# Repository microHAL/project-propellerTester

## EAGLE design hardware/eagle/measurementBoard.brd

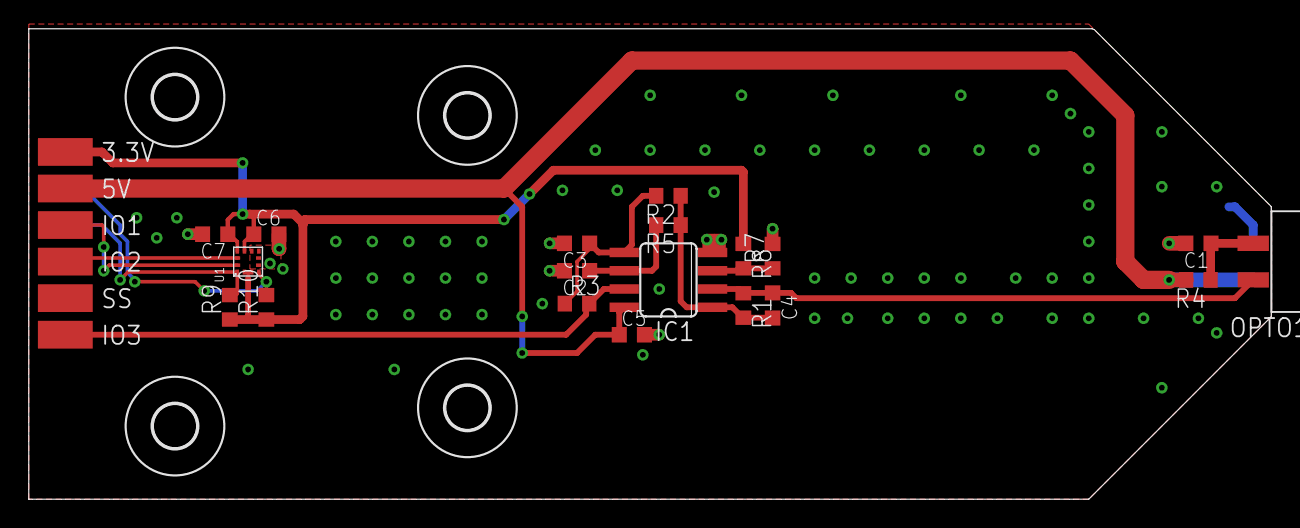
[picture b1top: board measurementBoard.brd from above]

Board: 2 copper layers, 86.3 x 32.7 mm, 25 parts (1 on the bottom side), 15 nets.

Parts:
C1: 2.2u; C0603K
C2: 10n; C0603K
C3, C4: 1n; C0603K
C5, C6, C7: 100n; C0603K
CON1: MICROHAL_CONNECTOR_M_1_REDUCED; MICROHAL_CONNECTOR_M_1_REDUCED_EDGE
H1, H2, H3, H4: MOUNT-HOLE3.0; 3,0
IC1: MAX989ESA; SO08
OPTO1: CNY70EDGE; CNY70_EDGE
R1, R6, R8: 3k; R0603
R2, R5: 100k; R0603
R3: 1M; R0603
R4: 100R; R0603
R7: DNF; R0603
R9, R10: 4.7k; R0603
U1: LGA-12

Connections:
+3V3: C6.1, C7.1, CON1.2, R8.1, R9.1, R10.1, U1.2, U1.3, U1.9, U1.10
+5V: C5.1, CON1.4, IC1.8, OPTO1.A, R4.2
GND: C1.2, C2.2, C3.2, C5.2, C6.2, C7.2, CON1.1, IC1.4, R6.2, R7.2, U1.5, U1.6, U1.7, U1.8
INT1: CON1.6, U1.12
INT2: CON1.8, U1.11
unnamed: C4.2, IC1.1, R1.2, R2.1, R5.1
unnamed: C4.1, IC1.2, OPTO1.E, R1.1
unnamed: C3.1, IC1.5, R2.2, R3.1
unnamed: C1.1, OPTO1.C, R4.1
unnamed: C2.1, IC1.6, R5.2
unnamed: OPTO1.K, R6.1
unnamed: IC1.3, R7.1, R8.2
OUT: CON1.12, IC1.7, R3.2
SCL: CON1.5, R9.2, U1.1
SDA: CON1.3, R10.2, U1.4

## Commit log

2016-01-26 Add initial directories
2016-01-26 added folders for propellerTester project
2016-01-30 Share project "Propeller tester firmware" into "https://svn.code.sf.net/p/microhal/drivers/Projects"
2016-01-30 added project template
2016-02-01 added measuring board
2016-02-06 added model of mechanical conception
2016-02-07 Added lis2dh12 and hx711 drivers to project.
2016-02-07 updated BSP configuration, enabled SPI and I2C device
2016-02-11 3D model updated
2016-02-13 added second version of hardware solution
2016-02-13 updated second version of mechanical montage
2016-02-15 added sk8 model
2016-03-18 added files to propellerTester PC application project
2016-03-22 Project creation.
2016-03-22 First sample program.
2016-03-22 Added linked resource - microHAL.
2016-03-27 added about dialog, changed main window gui
2016-03-27 Added class prototypes
2016-04-01 Added PCB project files, unfinished.
2016-04-01 Started implementing Timer interrupt in stepperMotor driver.
2016-04-01 Wired last connections.
2016-04-03 Probably ready for production.
2016-04-03 Rename.
2016-04-03 Rename, old files deletion.
2016-04-06 Modified connections between base SMT32F4-discovery and stepper motor driver.
2016-04-06 Instantiated a class for DRV8825.
2016-04-10 Added positionController class (draft).
2016-04-10 Added BT SPP source and header files (empty).
2016-04-10 Added diagnostic, configured and tested usart port.
2016-04-10 Added mutex, cosmetics.
2016-04-10 Added configuration for serial ports.
2016-04-10 Changed filename.
2016-04-10 Changed FTDI connection to the processor.
2016-04-11 silicon labs ports was excluded from build
2016-04-11 added esc driver file
2016-04-11 connected diagChannel to debugPort, added PPM driver
2016-04-11 enabled text in logging functions
2016-04-11 Działa!!!!!!!(belka i sterowanie esc)
2016-04-12 added version with spi based hx711 driver
2016-04-12 Poprawny przebieg na SPI
2016-04-14 Dzialajacy kod z tarowaniem
2016-04-14 Dodano skalowanie, ale do poprawy jest funkcja reset bo zwiesza mikrokontroler
2016-04-15 Drobne dodatki
2016-05-02 Deleted obsolete files.
2016-05-02 Working stepper motor direct controll with diagnostic.
2016-05-02 Working stepper motor direct controll.
2016-05-02 Working position controller, not calibrated properly.
2016-05-03 File renaming.
2016-05-28 Added externals component folder.
2016-05-28 Added microhal-cli module.
2016-05-28 Many old uncomminted changes...
2016-06-12 Progress and cleaning
2016-06-13 Progress
2016-06-13 Display all data on console(rpm,scaled force,rpm). Ideal for presentation
2016-06-30 Unknown old changes...
2016-07-13 Microhal configured as externals with new i2c api
2016-07-19 BSp for new board
2016-07-19 New main for testing
2016-07-20 Porting progress, gpio done, core in progress
2016-07-20 added clang format configuration file
2016-07-20 Led blinking works!!! and clock configuration progress
2016-07-21 IOManager implemented with serials
2016-07-24 Clock calculations update, not tested
2016-07-28 Share project "balloonObc" into "https://svn.code.sf.net/p/microhal/drivers/Projects/trunk/propellerTester/firmware"
2016-07-28 added folder for balloon project
2016-07-28 Share project "balloonObc" into "https://svn.code.sf.net/p/microhal/drivers/Projects"
2016-07-28 added externals: lepton driver; uCam II driver; freertos.
2016-07-28 updated bsp file
2016-07-29 updated bsp, added freertos
2016-08-04 added general CMD class
2016-08-08 added CID and CSD structures
2016-08-25 Usart works in polling mode
2016-08-29 Serial port works with interrupts
2016-08-31 Iomanager created for spi
2017-03-19 Added microhal as submodule
2017-03-19 Added building configuration for nucleo f334r8.
2017-03-20 Added HX711 to project.
